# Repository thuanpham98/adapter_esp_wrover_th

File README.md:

# ESP-WROVER_OPEN
## Hardware

### PCB Layout

#### Dismention 

#### Top side 

#### Back side 

### 3D

#### Top side 

#### Back side 

### Gerber

# License

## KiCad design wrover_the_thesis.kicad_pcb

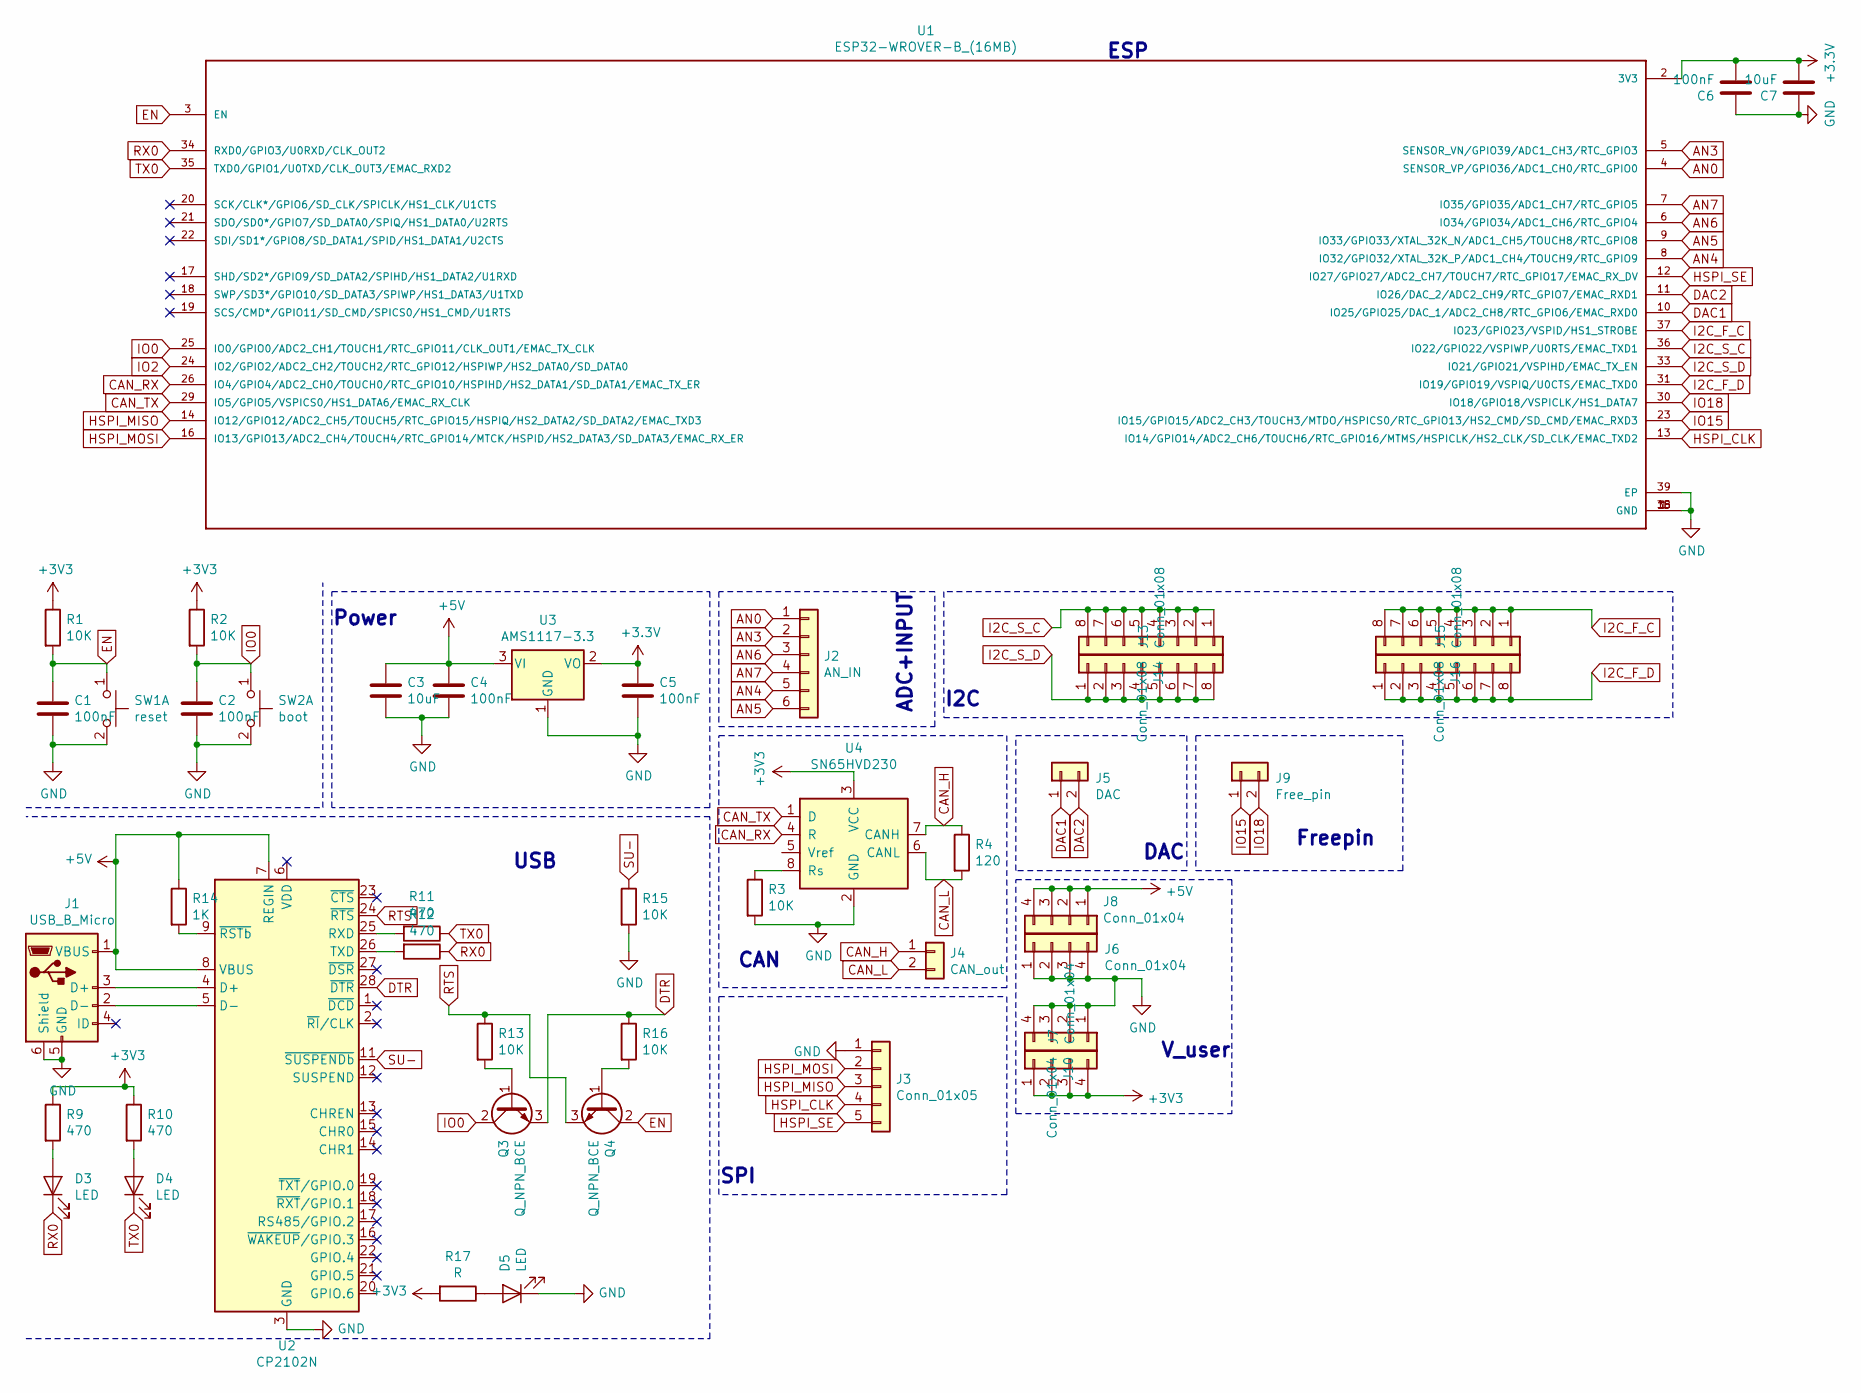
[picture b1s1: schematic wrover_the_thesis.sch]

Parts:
C1, C2, C4, C5, C6: 100nF; C_0603_1608Metric
C3: 10uF; R_1210_3225Metric
C7: 10uF; C_1210_3225Metric
D3, D4, D5: LED; LED_0603_1608Metric
J1: USB_B_Micro; USB_Micro-B_Wuerth_629105150521
J2: AN_IN; PinHeader_1x06_P2.54mm_Vertical
J3: Conn_01x05; PinHeader_1x05_P2.54mm_Vertical
J4: CAN_out; PinHeader_1x02_P2.54mm_Vertical
J5: DAC; PinHeader_1x02_P2.54mm_Vertical
J6, J7, J8, J10: Conn_01x04; PinSocket_1x04_P2.54mm_Vertical
J9: Free_pin; PinHeader_1x02_P2.54mm_Vertical
J13, J14, J15, J16: Conn_01x08; PinSocket_1x08_P2.54mm_Vertical
Q3, Q4: Q_NPN_BCE; SOT-23_standar
R1, R2, R3, R13, R15, R16: 10K; R_0603_1608Metric_Pad1.05x0.95mm_HandSolder
R4: 120; R_0603_1608Metric_Pad1.05x0.95mm_HandSolder
R9, R10, R11, R12: 470; R_0603_1608Metric_Pad1.05x0.95mm_HandSolder
R14: 1K; R_0603_1608Metric_Pad1.05x0.95mm_HandSolder
R17: R; R_0603_1608Metric_Pad1.05x0.95mm_HandSolder
SW1: reset; SW_SPST_CK_RS282G05A3
SW2: boot; SW_SPST_CK_RS282G05A3
U1: ESP32-WROVER-B_(16MB); XCVR_ESP32-WROVER-B_(16MB)
U2: CP2102N; QFN-28-1EP_5x5mm_P0.5mm_EP3.35x3.35mm
U3: AMS1117-3.3; SOT-223-3_TabPin2
U4: SN65HVD230; SOIC-8_3.9x4.9mm_P1.27mm

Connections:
+5V: C3.1, C4.1, J1.1 (VBUS), J8.1, J8.2, J8.3, J8.4, R14.1, U2.7 (REGIN), U2.8 (VBUS), U3.3 (VI)
AN0: J2.1, U1.4 (SENSOR_VP/GPIO36/ADC1_CH0/RTC_GPIO0)
AN3: J2.2, U1.5 (SENSOR_VN/GPIO39/ADC1_CH3/RTC_GPIO3)
AN4: J2.5, U1.8 (IO32/GPIO32/XTAL_32K_P/ADC1_CH4/TOUCH9/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)
AN5: J2.6, U1.9 (IO33/GPIO33/XTAL_32K_N/ADC1_CH5/TOUCH8/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)
AN6: J2.3, U1.6 (IO34/GPIO34/ADC1_CH6/RTC_GPIO4)
AN7: J2.4, U1.7 (IO35/GPIO35/ADC1_CH7/RTC_GPIO5)
CAN_H: J4.1, R4.1, U4.7 (CANH)
CAN_L: J4.2, R4.2, U4.6 (CANL)
CAN_RX: U1.26 (IO4/GPIO4/ADC2_CH0/TOUCH0/RTC_GPIO10/HS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), U4.4 (R)
CAN_TX: U1.29 (IO5/GPIO5/VSPICS0/HS1_DATA6/EMAC_RX_CLK), U4.1 (D)
DAC1: J5.1, U1.10 (IO25/GPIO25/DAC_1/ADC2_CH8/RTC_GPIO6/EM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)
DAC2: J5.2, U1.11 (IO26/DAC_2/ADC2_CH9/RTC_GPIO7/EMAC_RXD1)
DTR: Q3.3 (E), R16.1, U2.28 (~DTR)
EN: C1.1, Q4.2 (C), R1.2, SW1.1 (C), U1.3 (EN)
GND: C1.2, C2.2, C3.2, C4.2, C5.2, C6.1, C7.1, D5.1 (K), J1.5 (GND), J1.6 (Shield), J3.1, J6.1, J6.2, J6.3, J6.4, J10.1, J10.2, J10.3, J10.4, R3.2, R15.2, SW1.2 (D), SW2.2 (D), U1.1 (GND), U1.15 (GND), U1.38 (GND), U1.39 (EP), U2.3 (GND), U2.29 (GND), U3.1 (GND), U4.2 (GND)
HSPI_CLK: J3.4, U1.13 (IO14/GPIO14/ADC2_CH6/TOUCH6/RTC_GPIO16/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)
HSPI_MISO: J3.3, U1.14 (IO12/GPIO12/ADC2_CH5/TOUCH5/RTC_GPIO15/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)
HSPI_MOSI: J3.2, U1.16 (IO13/GPIO13/ADC2_CH4/TOUCH4/RTC_GPIO14/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)
HSPI_SE: J3.5, U1.12 (IO27/GPIO27/ADC2_CH7/TOUCH7/RTC_GPIO17/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)
I2C_F_C: J16.1, J16.2, J16.3, J16.4, J16.5, J16.6, J16.7, J16.8, U1.37 (IO23/GPIO23/VSPID/HS1_STROBE)
I2C_F_D: J15.1, J15.2, J15.3, J15.4, J15.5, J15.6, J15.7, J15.8, U1.31 (IO19/GPIO19/VSPIQ/U0CTS/EMAC_TXD0)
I2C_S_C: J14.1, J14.2, J14.3, J14.4, J14.5, J14.6, J14.7, J14.8, U1.36 (IO22/GPIO22/VSPIWP/U0RTS/EMAC_TXD1)
I2C_S_D: J13.1, J13.2, J13.3, J13.4, J13.5, J13.6, J13.7, J13.8, U1.33 (IO21/GPIO21/VSPIHD/EMAC_TX_EN)
IO0: C2.1, Q3.2 (C), R2.2, SW2.1 (C), U1.25 (IO0/GPIO0/ADC2_CH1/TOUCH1/RTC_GPIO11/CL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)
IO15: J9.1, U1.23 (IO15/GPIO15/ADC2_CH3/TOUCH3/MTDO/HSPICS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)
IO18: J9.2, U1.30 (IO18/GPIO18/VSPICLK/HS1_DATA7)
unnamed: D3.2 (A), R9.2
unnamed: D4.2 (A), R10.2
unnamed: D5.2 (A), R17.1
unnamed: J1.2 (D-), U2.5 (D-)
unnamed: J1.3 (D+), U2.4 (D+)
unnamed: Q3.1 (B), R13.2
unnamed: Q4.1 (B), R16.2
unnamed: R3.1, U4.8 (Rs)
unnamed: R11.2, U2.25 (RXD)
unnamed: R12.2, U2.26 (TXD)
unnamed: R14.2, U2.9 (~RSTb)
RTS: Q4.3 (E), R13.1, U2.24 (~RTS)
RX0: D3.1 (K), R12.1, U1.34 (RXD0/GPIO3/U0RXD/CLK_OUT2)
SU-: R15.1, U2.11 (~SUSPENDb)
TX0: D4.1 (K), R11.1, U1.35 (TXD0/GPIO1/U0TXD/CLK_OUT3/EMAC_RXD2)

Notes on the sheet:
Power
ESP
USB
ADC+INPUT
CAN
SPI
I2C
DAC
Freepin
V_user

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
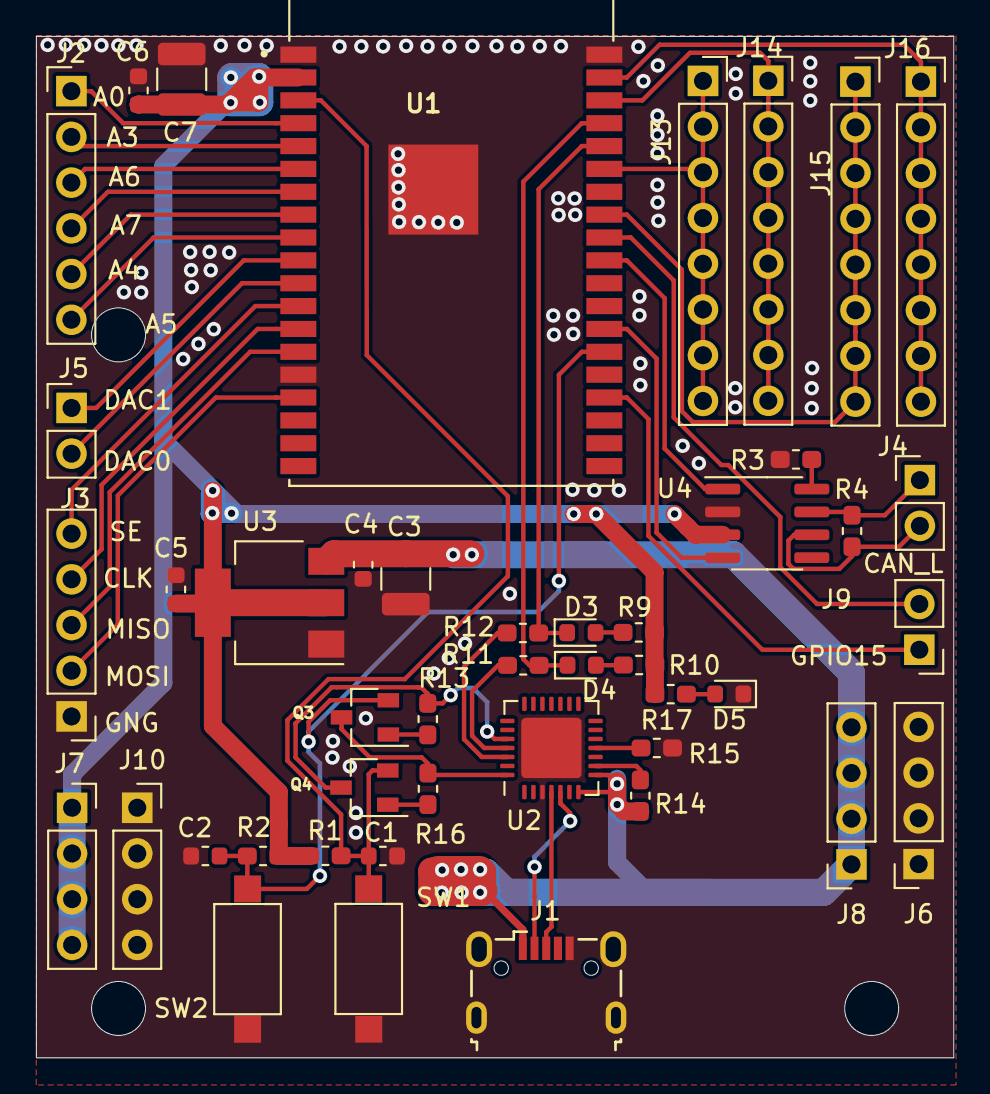
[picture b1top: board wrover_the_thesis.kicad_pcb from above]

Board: 2 copper layers, 51.0 x 56.7 mm, 45 parts (0 on the bottom side), 43 nets.
